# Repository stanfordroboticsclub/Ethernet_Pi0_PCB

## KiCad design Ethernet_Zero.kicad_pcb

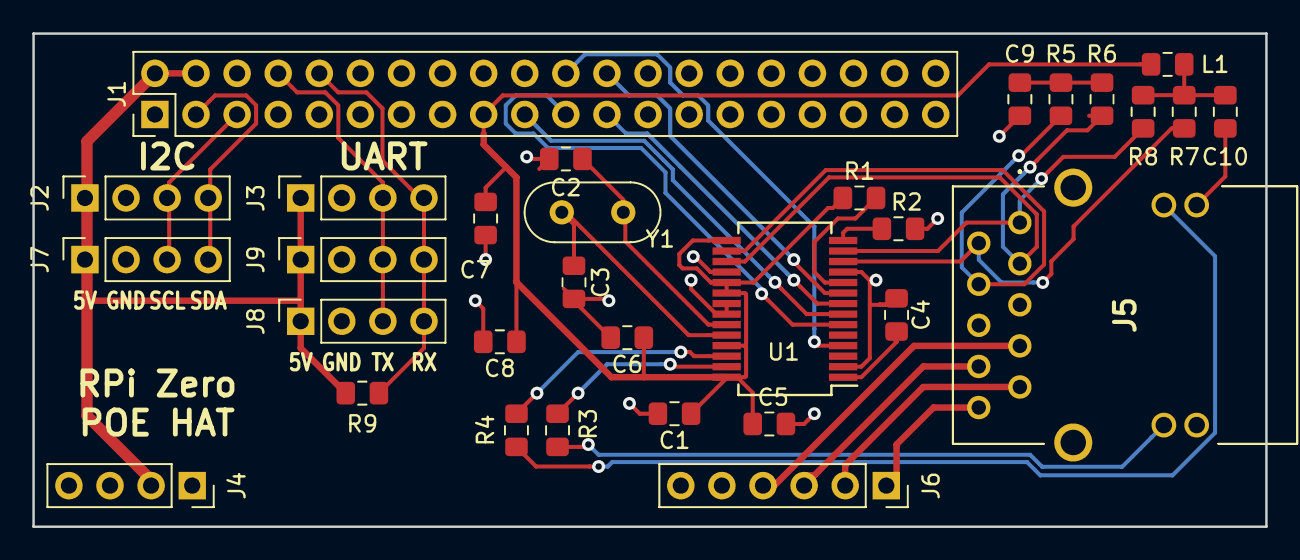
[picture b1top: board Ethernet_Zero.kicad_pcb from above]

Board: 2 copper layers, 76.2 x 30.5 mm, 31 parts (0 on the bottom side), 31 nets.

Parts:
C1, C5, C6, C7, C8, C9, C10: 100nF; C_0805_2012Metric_Pad1.15x1.40mm_HandSolder
C2, C3: 10pF; C_0805_2012Metric_Pad1.15x1.40mm_HandSolder
C4: 10uF; C_0805_2012Metric_Pad1.15x1.40mm_HandSolder
J1: Raspberry_Pi_2_3; PinHeader_2x20_P2.54mm_Vertical
J2, J7: I2C; PinSocket_1x04_P2.54mm_Vertical
J3, J8, J9: UART; PinSocket_1x04_P2.54mm_Vertical
J4: POE_5V; PinSocket_1x04_P2.54mm_Vertical
J5: ARJM11C7-104-AB-EW2; ARJM11C7104ABEW2
J6: POE_48V; PinSocket_1x06_P2.54mm_Vertical
L1: L_Core_Ferrite; L_0805_2012Metric_Pad1.15x1.40mm_HandSolder
R1: 10k; R_0805_2012Metric_Pad1.15x1.40mm_HandSolder
R2: 2k / 1%; R_0805_2012Metric_Pad1.15x1.40mm_HandSolder
R3, R4: 100; R_0805_2012Metric_Pad1.15x1.40mm_HandSolder
R5, R6, R7, R8: 49.9 / 1%; R_0805_2012Metric_Pad1.15x1.40mm_HandSolder
R9: 1k; R_0805_2012Metric_Pad1.15x1.40mm_HandSolder
U1: ENC28J60x-SS; SSOP-28_5.3x10.2mm_P0.65mm
Y1: Crystal 25MHz; Crystal_HC52-6mm_Vertical

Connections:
+3V3: C1.1, C5.1, C6.1, C7.1, C8.1, J1.17, L1.1, R1.1, U1.15, U1.19, U1.20, U1.25, U1.28
/5v: J1.2, J1.4, J2.1, J3.1, J4.2, J7.1, J8.1, J9.1, R9.1
/LED_GREEN: R3.1, U1.27
/LED_YELLOW: R4.1, U1.26
/VC1+: J5.7, J6.4
/VC1-: J5.8, J6.3
/VC2+: J5.9, J6.2
/VC2-: J5.10, J6.1
/rx: J1.10, J3.4, J8.4, J9.4, R9.2
/scl: J1.5, J2.3, J7.3
/sda: J1.3, J2.4, J7.4
/tx: J1.8, J3.3, J8.3, J9.3
/~INT: J1.22, U1.4
GND: C1.2, C2.2, C3.2, C4.2, C5.2, C6.2, C7.2, C8.2, C9.2, C10.1, J1.20, J2.2, J3.2, J4.1, J5.L2, J5.L4, J5.MH1, J5.MH2, J7.2, J8.2, J9.2, R2.2, U1.2, U1.11, U1.18, U1.21, U1.22
unnamed: C2.1, U1.23, Y1.1
unnamed: C3.1, U1.24, Y1.2
unnamed: C4.1, U1.1
unnamed: C9.1, R5.2, R6.2
unnamed: C10.2, L1.2, R7.1, R8.1
unnamed: J1.19, U1.7
unnamed: J1.21, U1.6
unnamed: J1.23, U1.8
unnamed: J1.24, U1.9
unnamed: J5.1, R8.2, U1.13
unnamed: J5.2, R7.2, U1.12
unnamed: J5.3, R6.1, U1.17
unnamed: J5.4, R5.1, U1.16
unnamed: J5.L1, R3.2
unnamed: J5.L3, R4.2
unnamed: R1.2, U1.10
unnamed: R2.1, U1.14

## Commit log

2020-01-24 initial comit
